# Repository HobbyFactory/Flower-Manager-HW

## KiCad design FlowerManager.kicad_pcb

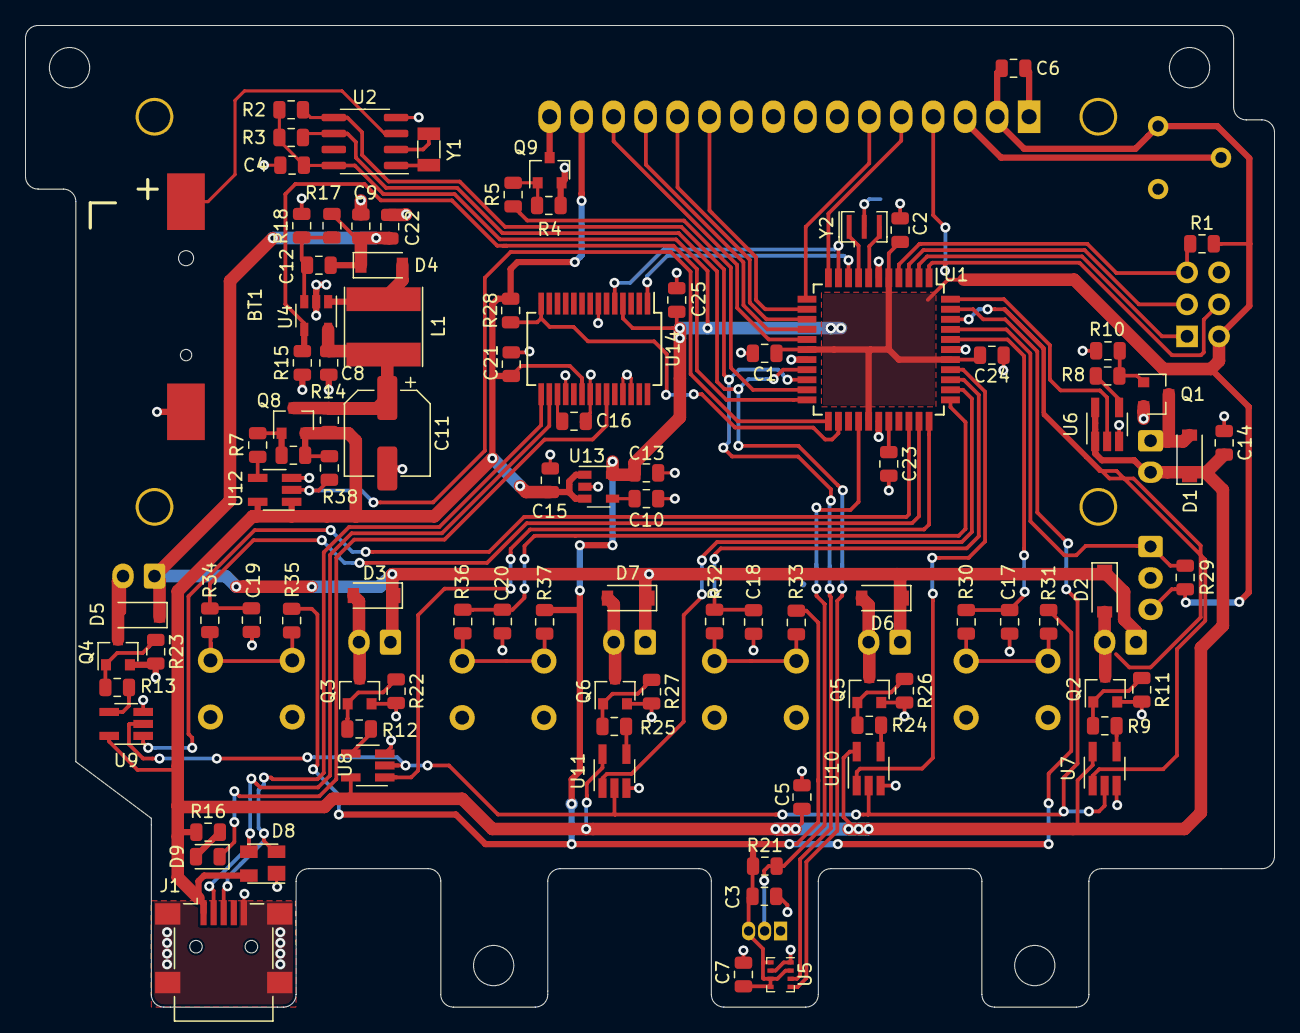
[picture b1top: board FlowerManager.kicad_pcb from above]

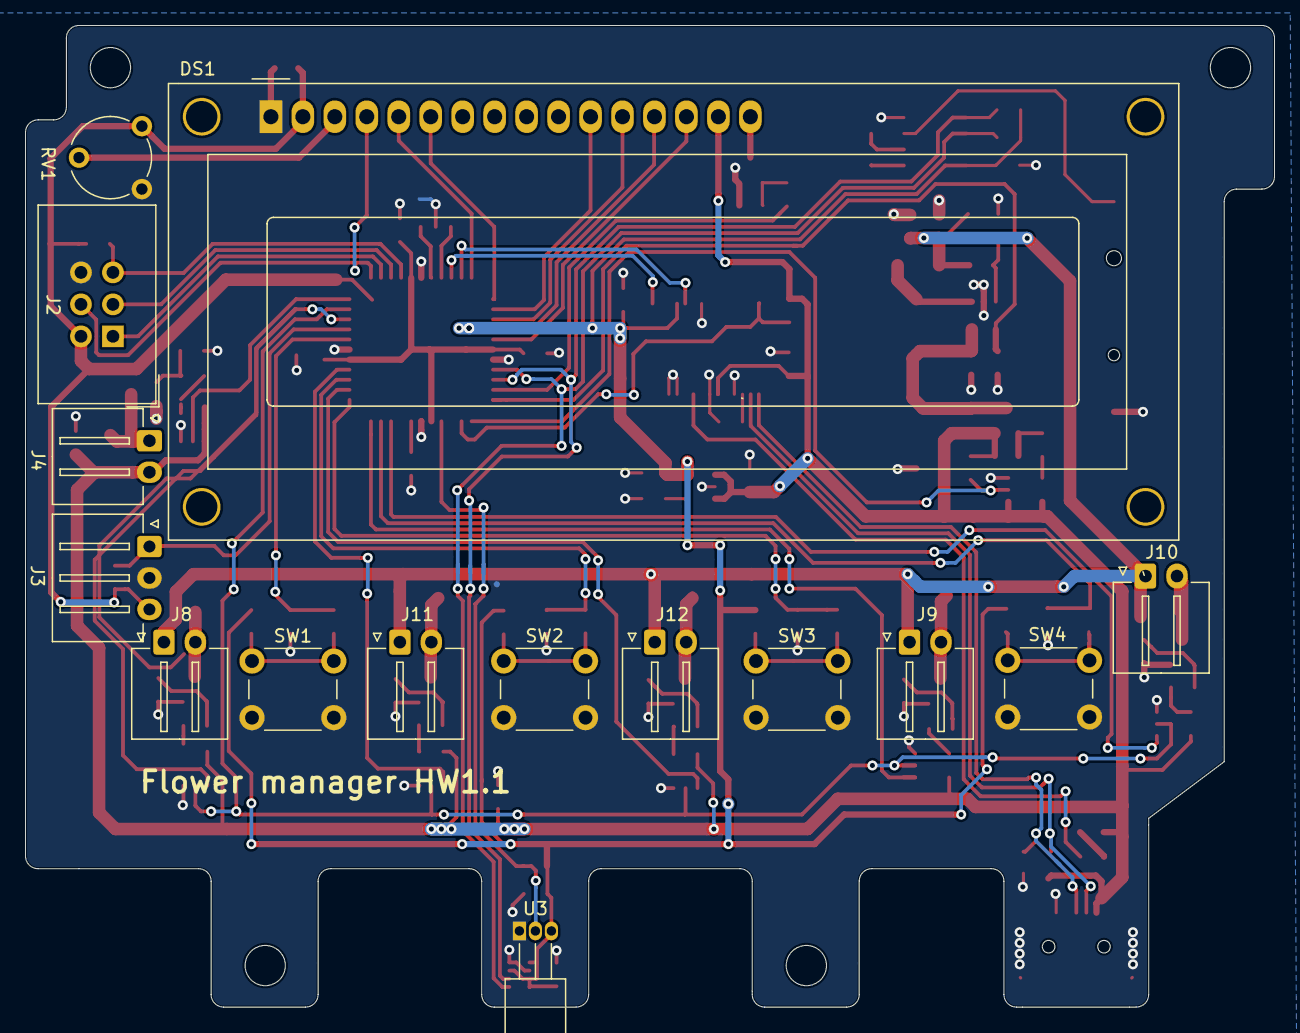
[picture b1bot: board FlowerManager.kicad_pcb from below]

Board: 2 copper layers, 99.2 x 78.0 mm, 115 parts (19 on the bottom side), 77 nets.

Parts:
BT1: Battery_Cell; BatteryHolder_CR1220
C1, C2, C3, C4, C5, C6, C7, C8, C14, C15, C16, C21, C23, C24, C25: 100nF/50V; C_0805_2012Metric
C9, C13, C22: 10uF/16V; C_0805_2012Metric
C10, C17, C18, C19, C20: 10nF/50V; C_0805_2012Metric
C11: 220uF/10V; CP_Elec_6.3x5.4
C12: n.a.; C_0805_2012Metric
D1, D2, D3, D5, D6, D7: MBR0520; D_SOD-123
D4: MBR0520LT; D_SOD-123
D8: SP0503BAHT; SOT-143
D9: LED; LED_0805_2012Metric
DS1: WC1602A; LCD_2x16_HD44780_Ebay
H1, H2, H3, H4: MountingHole; MountingHole_3.2mm_M3
J1: USB_B_Mini; USB_Mini-B_Lumberg_2486_01_Horizontal
J2: AVR-ISP-6; IDC-Header_2x03_P2.54mm_Vertical
J3: Conn_01x03_Male; JST_XH_S03B_ChinaLowCost
J4, J8, J9, J10, J11, J12: Conn_01x02_Male; JST_XH_S02B_ChinaLowCost
L1: 10uH; L_InductorSimple_5x5mm
Q1, Q2, Q3, Q4, Q5, Q6, Q9: AO3406; SOT-23
Q8: IRLML6402; SOT-23
R1, R4, R6, R10, R11, R22, R23, R26, R27, R28, R29, R31, R33, R35, R37: 8k2; R_0805_2012Metric
R2, R3, R15, R21, R38: 4k7; R_0805_2012Metric
R5, R7, R8, R9, R12, R13, R24, R25: 120R; R_0805_2012Metric
R14, R30, R32, R34, R36: 100R; R_0805_2012Metric
R16: 270R; R_0805_2012Metric
R17: 82k; R_0805_2012Metric
R18: 10k; R_0805_2012Metric
RV1: 10k; Potentiometer_Piher_PT-6-V_Vertical
SW1, SW2, SW3, SW4: SW_Push; SW_PUSH_6mm_H5mm
U1: ATmega324PA-AU; TQFP-44_10x10mm_P0.8mm
U2: DS1307Z+; SOIC-8_3.9x4.9mm_P1.27mm
U3: DS18B20; TO-92_Inline_Horizontal1
U4: LM27313YMF; SOT-23-5
U5: BMP280; Bosch_LGA-8_2x2.5mm_P0.65mm_ClockwisePinNumbering
U6, U7, U8, U9, U10, U11, U12: 74LVC1G08; SOT-23-5_HandSoldering
U13: LP2985-3.3; SOT-23-5
U14: FT232RL; SSOP-28_5.3x10.2mm_P0.65mm
Y1: FC135; Crystal_SMD_FC135
Y2: Resonator; Resonator_SMD_muRata_CSTxExxV-3Pin_3.0x1.1mm_with3D

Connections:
+3V3: C1.1, C2.1, C3.2, C4.1, C6.2, C7.2, C13.1, C24.2, C25.1, DS1.2, J2.2, J3.3, R1.1, R2.1, R3.1, R21.1, R29.1, R31.1, R33.1, R35.1, R37.1, RV1.1, U1.5, U1.17, U1.27, U1.38, U2.8, U3.3, U5.2, U5.5, U5.6, U5.8, U13.5, U14.4
+5V: C5.1, C14.2, C15.2, C21.1, D1.1, D8.4, DS1.15, J1.1, J4.2, Q8.2, R6.2, R14.2, R16.1, R28.1, R38.2, U6.1, U6.5, U7.5, U8.5, U9.5, U10.5, U11.5, U12.1, U12.5, U13.1, U13.3, U14.20
+5VP: C8.2, C11.1, L1.1, Q8.3, R14.1, U4.5
+10V: C9.1, C12.1, C22.1, D2.1, D3.1, D4.1, D5.1, D6.1, D7.1, J8.1, J9.1, J10.1, J11.1, J12.1, R17.1
/USB-UART/LED_TX: D9.1, U14.23
/USB-UART/USBDM: D8.3, J1.2, U14.16
/USB-UART/USBDP: D8.2, J1.3, U14.15
/X1: U1.8, Y2.1
/X2: U1.7, Y2.3
COMMON_PWM: U1.43, U7.2, U8.2, U9.2, U10.2, U11.2
DB4: DS1.11, U1.13
DB5: DS1.12, U1.14
DB6: DS1.13, U1.15
DB7: DS1.14, U1.16
E: DS1.6, U1.12
EN_BACKLIGHT: R5.1, U1.21
EN_BOOST: R15.2, U1.22, U4.4
EN_INRSH: R38.1, U1.23, U12.2
EN_PUMP: U1.44, U6.2
EN_VALVE1: U1.42, U7.1
EN_VALVE2: U1.37, U10.1
EN_VALVE3: U1.35, U11.1
EN_VALVE4: U1.33, U8.1
EN_VALVE5: U1.31, U9.1
FLOW_SNS: J3.1, R29.2, U1.41
GND: BT1.2, C1.2, C2.2, C3.1, C4.2, C5.2, C6.1, C7.1, C8.1, C9.2, C10.2, C11.2, C13.2, C14.1, C15.1, C16.2, C17.2, C18.2, C19.2, C20.2, C21.2, C22.2, C23.2, C24.1, C25.2, D8.1, DS1.1, J1.5, J1.6, J2.6, J3.2, Q1.2, Q2.2, Q3.2, Q4.2, Q5.2, Q6.2, Q9.2, R4.2, R10.2, R11.2, R15.1, R18.2, R22.2, R23.2, R26.2, R27.2, RV1.3, SW1.2, SW2.2, SW3.2, SW4.2, U1.6, U1.18, U1.28, U1.39, U2.4, U3.1, U4.2, U5.1, U5.7, U6.3, U7.3, U8.3, U9.3, U10.3, U11.3, U12.3, U13.2, U14.7, U14.18, U14.21, U14.25, U14.26, Y2.2
MISO: J2.1, U1.2
MOSI_&_RS: DS1.4, J2.4, U1.1
unnamed: BT1.1, U2.3
unnamed: C10.1, U13.4
unnamed: C12.2, R17.2, R18.1, U4.3
unnamed: C16.1, U14.17
unnamed: C23.1, U1.29
unnamed: D1.2, J4.1, Q1.3
unnamed: D2.2, J8.2, Q2.3
unnamed: D3.2, J9.2, Q3.3
unnamed: D4.2, L1.2, U4.1
unnamed: D5.2, J10.2, Q4.3
unnamed: D6.2, J11.2, Q5.3
unnamed: D7.2, J12.2, Q6.3
unnamed: D9.2, R16.2
unnamed: DS1.3, RV1.2
unnamed: DS1.16, Q9.3
unnamed: Q1.1, R8.2, R10.1
unnamed: Q2.1, R9.2, R11.1
unnamed: Q3.1, R12.2, R22.1
unnamed: Q4.1, R13.2, R23.1
unnamed: Q5.1, R24.2, R26.1
unnamed: Q6.1, R25.2, R27.1
unnamed: Q8.1, R6.1, R7.2
unnamed: Q9.1, R4.1, R5.2
unnamed: R7.1, U12.4
unnamed: R8.1, U6.4
unnamed: R9.1, U7.4
unnamed: R12.1, U8.4
unnamed: R13.1, U9.4
unnamed: R24.1, U10.4
unnamed: R25.1, U11.4
unnamed: R30.1, R31.2, SW1.1
unnamed: R32.1, R33.2, SW2.1
unnamed: R34.1, R35.2, SW4.1
unnamed: R36.1, R37.2, SW3.1
unnamed: U2.1, Y1.1
unnamed: U2.2, Y1.2
PWREN: R28.2, U1.24, U14.14
RST: J2.5, R1.2, U1.4
RW: DS1.5, U1.11
RxD: U1.9, U14.1
SCK: J2.3, U1.3
SCL: R3.2, U1.19, U2.6, U5.4
SDA: R2.2, U1.20, U2.5, U5.3
SW1: C17.1, R30.2, U1.40
SW2: C18.1, R32.2, U1.36
SW3: C20.1, R36.2, U1.34
SW4: C19.1, R34.2, U1.32
TEMP_SENSOR: R21.2, U1.26, U3.2
TxD: U1.10, U14.5

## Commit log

2020-07-11 fixed library rescue problem in schematic
